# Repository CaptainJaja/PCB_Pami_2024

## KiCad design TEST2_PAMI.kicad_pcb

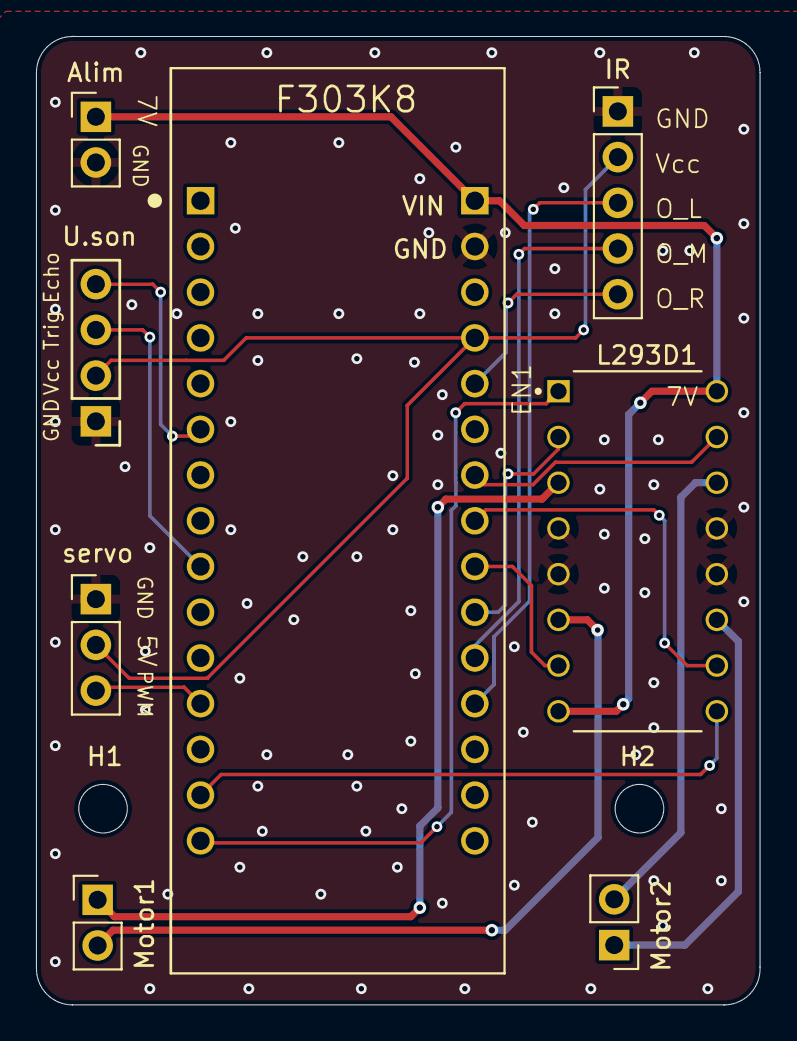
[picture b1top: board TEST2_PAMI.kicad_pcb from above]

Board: 2 copper layers, 40.2 x 53.8 mm, 10 parts (0 on the bottom side), 19 nets.

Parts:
Alim: PinHeader_1x02_P2.54mm_Vertical
F303K8: MODULE_NUCLEO-F303K8
H1, H2: MountingHole_Pad; MountingHole_2.7mm_M2.5
IR: PinHeader_1x05_P2.54mm_Vertical
L293D1: L293D; L293D_Motor_Driver
Motor1, Motor2: PinHeader_1x02_P2.54mm_Vertical
U.son: PinHeader_1x04_P2.54mm_Vertical
servo: PinHeader_1x03_P2.54mm_Vertical

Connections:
/5V: F303K8.4_4 (5V), IR.2 (VCC), U.son.2 (Vcc), servo.1 (GND)
/7V: Alim.1 (7V), F303K8.4_1 (VIN), L293D1.8 (VS), L293D1.16 (VSS)
/EN1: F303K8.3_15 (PB_4), L293D1.1 (ENABLE1)
/EN2: F303K8.3_14 (PB_5), L293D1.9 (ENABLE2)
/Echo: F303K8.3_6 (PB_0), U.son.4 (Echo)
/GND: Alim.2 (GND), F303K8.4_2 (GND), IR.1 (GND), L293D1.4 (GND), L293D1.5 (GND), L293D1.12 (GND), L293D1.13 (GND), U.son.1 (GND), servo.2 (5V)
/IN1: F303K8.4_10 (PA_3), L293D1.2 (INPUT1)
/IN2: F303K8.4_9 (PA_4), L293D1.7 (INPUT2)
/IN3: F303K8.4_8 (PA_5), L293D1.10 (INPUT3)
/IN4: F303K8.4_7 (PA_6), L293D1.15 (INPUT4)
/O_L: F303K8.4_12 (PA_0), IR.3 (O_L)
/O_M: F303K8.4_11 (PA_1), IR.4 (O_M)
/O_R: F303K8.4_5 (PA_2), IR.5 (O_R)
/Trig: F303K8.3_9 (PB_1), U.son.3 (Trig)
/out1: L293D1.3 (OUTPUT1), Motor1.1 (input1)
/out2: L293D1.6 (OUTPUT2), Motor1.2 (input2)
/out3: L293D1.11 (OUTPUT3), Motor2.1 (input1)
/out4: L293D1.14 (OUTPUT4), Motor2.2 (input2)
/pwm_servo: F303K8.3_12 (PA_8), servo.3 (PWM)
